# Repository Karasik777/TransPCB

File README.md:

# TransPCB

Agent-driven KiCad PCB design. You describe the board; Claude does schematic
capture, placement, autorouting and verification — under constraints you declare
once in a file.

Built by working a real board end to end, and hardened against every way that
went wrong. The [gotchas](docs/gotchas.md) are the actual value here: eight
documented failures that no upstream tool warns you about, three of which were
live on a board while KiCad DRC reported **zero errors**.

## What you get

- **7 Claude skills** — from-scratch design, routing, verification, optimisation,
  fab output, and the constraint system that ties them together
- **A constraint spec** — fab limits, net classes, differential pairs, via
  budgets, impedance targets, RF keepouts — declared once, pushed down to the
  autorouter, KiCad's rules, and the verifier
- **A verification suite** that catches what DRC misses: board-vs-schematic net
  drift, copper in RF keepouts, pair skew and via asymmetry, drill/annular DFM,
  missing ground planes, design-rule tampering — and **thermal**, which found
  the example board's regulator at 120 °C junction against a 125 °C limit
- **Thresholds derived from physics, not constants.** Declare `interface:
  usb2.0-fs` and the skew budget follows from the edge rate (20 mm), not from a
  number somebody typed
- **A crash guard** for a KiCad 10.0.5 segfault that kills the app mid-session
- **A placement critic** that reads your netlist and scores decoupling distance,
  decap ordering, connector edge access, crystal proximity and keepouts — with
  thresholds that tighten by frequency band
- **A placement optimiser** — simulated annealing against a tunable cost
  function. On the example board it cut copper 772→661 mm, vias 92→42, and
  moved the ESP32's decoupling cap from 22 mm to 4 mm from the pin it serves
- **Current-aware track widths** (IPC-2221) and a stackup gate, so an impedance
  target either uses your real stack or refuses to run
- **A fab package** gated on clean DRC — gerbers, drill, BOM, JLCPCB CPL
- **A worked example** — ESP32-C3 dev board, with its routing animation

## Install

```bash
git clone https://github.com/Karasik777/TransPCB && cd TransPCB
./setup/install.sh --project /path/to/your/board
```

Installs pinned versions of [`kicad-mcp-pro`](https://github.com/oaslananka/kicad-mcp-pro),
[`KiCadRoutingTools`](https://github.com/drandyhaas/KiCadRoutingTools), the
Freerouting container and the Python deps, then links the skills into
`~/.claude/skills/`. Nothing is vendored — upstream keeps its own updates.

Needs KiCad 9 or 10, `uv`, and optionally Docker. See [docs/mcp-setup.md](docs/mcp-setup.md).

## Use

```bash
cp constraints/example.yaml myboard/constraints.yaml    # edit it
```

Then just ask:

> Build me an ESP32-C3 dev board: USB-C power and native USB data, an efficient
> LDO, ESD protection, buttons, GPIO headers, test points. JLCPCB standard,
> 2 layers, as small as you can.

or, on a board that already exists:

> Route this board. Keep vias under 60, USB as a matched pair, ground plane on
> both layers, nothing under the antenna.

Anything after the verb belongs in `constraints.yaml` — say it once there and it
reaches the router, KiCad's rules and the verifier together.

## The loop

```
preflight  ->  commit  ->  apply constraints  ->  act  ->  verify  ->  commit
```

`git commit` before every routing run is not optional. Both autorouters and an
open pcbnew window have each silently destroyed a complete routing pass.

## Routers

| | Freerouting 2.1.0 | Rust A* |
|---|---|---|
| Routing violations | 1 unconnected, 2 dangling stubs | **0** |
| Copper | 958.3 mm | **691.7 mm** |
| Vias | **17** | 41 |
| Runtime | **58 s** (`-mp 20`, measured) | **0.18 s** — ~320x faster |
| Workflow | 2 manual GUI steps | none — reads `.kicad_pcb` |

Rust A* is the default. It also rewrites your design rules and discards copper
zones, so the workflow repairs both after every run — see
[pcb-route](skills/pcb-route/SKILL.md).

## Layout

```
skills/       Claude skills — the automation surface
scripts/
  kicad_sexp.py        s-expression reader/writer everything else builds on
  apply_constraints.py spec -> KiCad rules + router flags + IPC-2221 widths
  verify.py            net sync, keepouts, pair skew, DFM, planes, rule drift
  place_rules.py       placement critic, band-aware EE guidelines
  place_optimise.py    simulated-annealing placement refinement
  probe_footprint.py   pad axis, origin, courtyard, mating face — before placing
  fill_zones.py        headless zone fill (kicad-cli has none)
  fab_package.py       gerbers/drill/BOM/CPL, gated on clean DRC
  preflight.sh         crash guard + stale-buffer guard
constraints/  the spec schema, documented inline
docs/         MCP setup, gotchas, workflow
setup/        pinned installer, versions.lock
examples/     ESP32-C3 dev board + routing animation
```

## Credits

- [kicad-mcp-pro](https://github.com/oaslananka/kicad-mcp-pro) — Osman Aslan (MIT)
- [KiCadRoutingTools](https://github.com/drandyhaas/KiCadRoutingTools) — drandyhaas (MIT)
- [Freerouting](https://github.com/freerouting/freerouting) (GPL)
- [KiCad](https://kicad.org)

MIT. See [LICENSE](LICENSE).

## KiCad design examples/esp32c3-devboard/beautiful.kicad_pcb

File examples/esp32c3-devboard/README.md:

# ESP32-C3 dev board

The board TransPCB was built while making. 2 layers, 30 x 60 mm, JLCPCB standard.

## What's on it

- **U1** ESP32-C3-WROOM-02, antenna at the top board edge with a copper keepout
- **J3** USB-C, right-angle through-hole (GCT USB4085), 5.1k CC pulldowns
- **U3** USBLC6-2SC6 ESD clamp on D+/D- and VBUS
- **U2** AP2112K-3.3 LDO; CP1 100uF radial bulk, C4/C5 in, C6/C7 out
- Native USB Serial/JTAG on IO18/IO19 - **no UART bridge chip**
- RESET and BOOT buttons, power LED plus two user LEDs, six test points
- **J1/J2** 1x10 headers, pinout matched to the module's pin geography

## Header pinout

Deliberately arranged so each header carries the module pins physically nearest
it. Getting this wrong forces nets across the whole board and makes a 2-layer
route impossible without cutting the ground plane.

| J1 (left) | J2 (right) |
|---|---|
| 1 +3V3 · 2 GND | 1 +3V3 · 2 GND |
| 3 IO4 · 4 IO5 · 5 IO6 · 6 IO7 | 3 IO0 · 4 IO1 · 5 IO2 · 6 IO3 |
| 7 IO8 · 8 IO9 | 7 IO21/TX · 8 IO20/RX · 9 IO10 |
| 9 GND · 10 +3V3 | 10 EN |

## Reproducing

```bash
cp -r examples/esp32c3-devboard /tmp/demo && cd /tmp/demo
../../scripts/preflight.sh beautiful.kicad_pcb
python ../../scripts/verify.py beautiful.kicad_pcb --spec constraints.yaml --sch beautiful.kicad_sch
```

## Routing animation

`media/routing.gif` - 46 frames replaying the router's own event log
(`KICAD_ROUTE_TRACE=1`), showing traces laid, ripped and restored. Open it in a
browser; some image viewers show only the first frame.

## State

**0 DRC errors, 0 unconnected pads.** 5 of 6 TransPCB checks pass.

Placement was refined by `place_optimise.py` (simulated annealing) and fully
re-routed. Against the hand-placed original:

| | hand-placed | optimised |
|---|---|---|
| copper | 772.4 mm | **661.0 mm** |
| vias | 92 | **42** |
| ESP32 3V3 pin to nearest 100 nF | 22.00 mm | **4.09 mm** |
| DRC errors | 0 | **0** |

That last row is the one that matters: decoupling 22 mm from the pin it serves
is ornamental. It also drove four fixes in the optimiser - see the
`pcb-place` skill.

Routed with the two-stage flow - `route_diff.py` for the USB pair first, then
`route.py` for the rest. Pair skew: connector side 7.39 -> 3.26 mm, MCU side
13.42 -> 5.16 mm against a single-ended first attempt.

A board-level `ANTENNA_KEEPOUT` zone (tracks, vias and pour not allowed) keeps
the RF region clear - the router respects it, rather than the verifier catching
intrusions afterwards. Its boundary is y=61.5 rather than the footprint's 61.9,
because U1's own pads sit at y=62.0 and a 0.4 mm track reaching them spans
61.8..62.2.

### The one accepted failure

`diffpair:USB` - copper skew **2.89 mm** against a 2.5 mm threshold
(`USB_DP` 85.19 mm / 2 vias, `USB_DM` 82.29 mm / 4 vias).

This is the term that regressed when placement was optimised for decoupling:
skew was 1.52 mm before. A deliberate trade, and the right one here - at 12 Mbps
full-speed a bit period is 83 ns, and 2.9 mm of FR4 is roughly 19 ps, under
0.03% of a bit. USB 2.0 full speed also has no impedance-matching requirement;
that begins at high speed, 480 Mbps.

It would matter on a faster interface or in EMC testing. Fixing it properly
means placement work around TP3/TP4 and the ESD part, not re-routing.

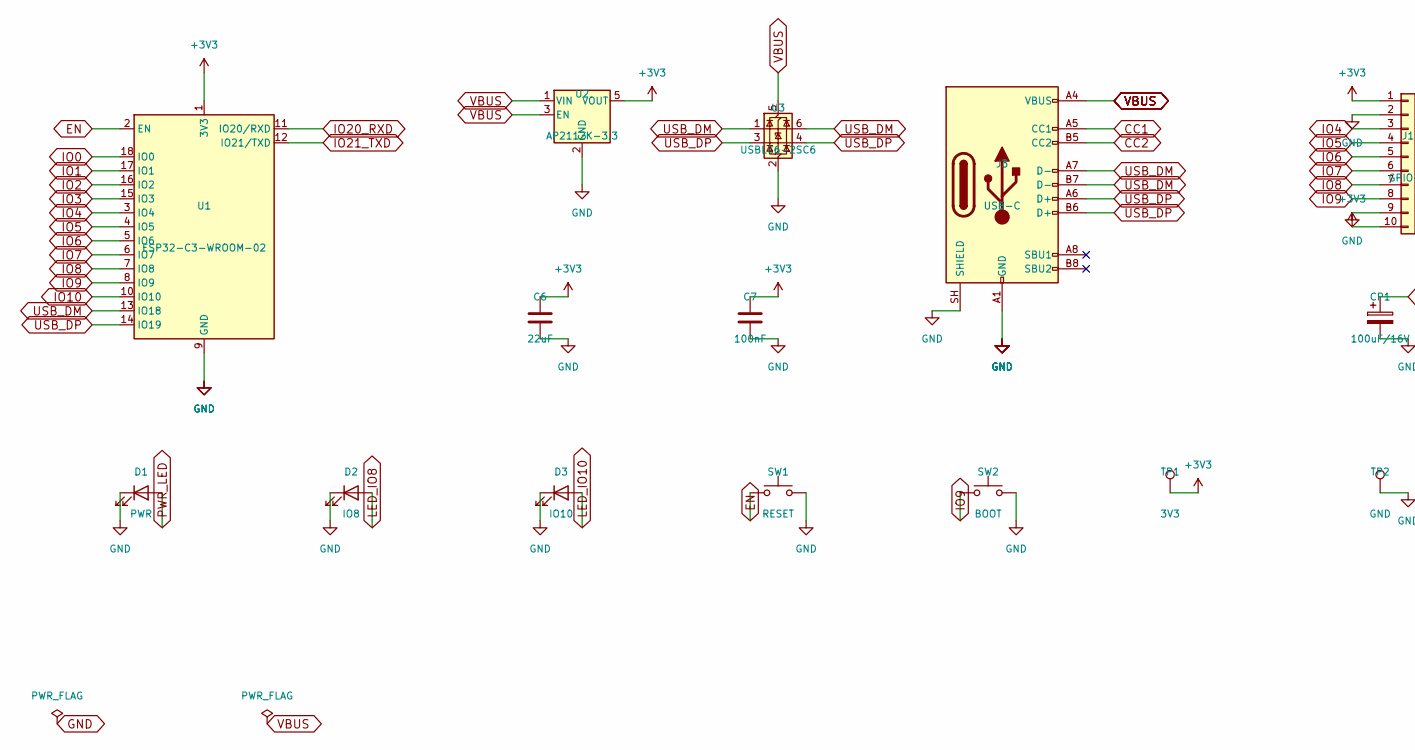
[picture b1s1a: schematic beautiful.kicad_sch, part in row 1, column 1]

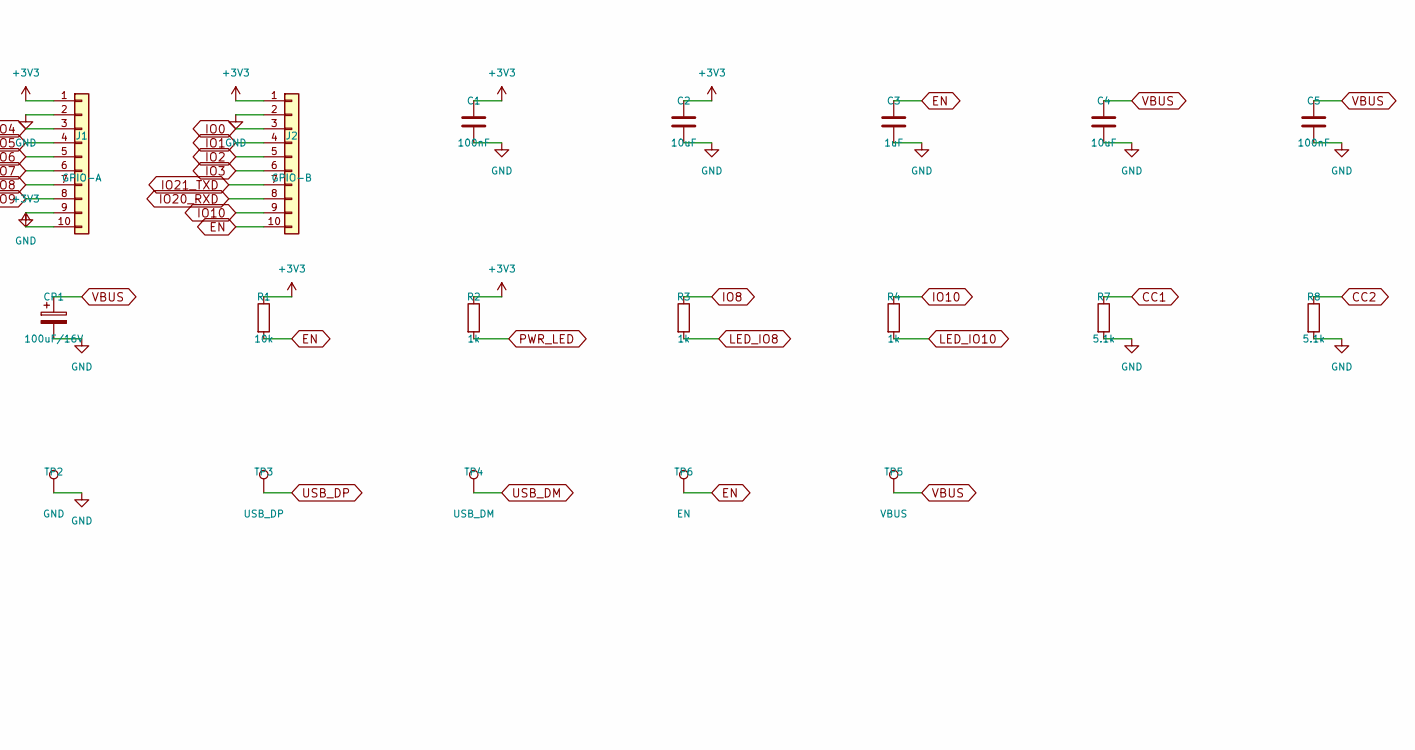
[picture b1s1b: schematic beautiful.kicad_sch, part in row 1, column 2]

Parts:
C1, C5, C7: 100nF; C_0603_1608Metric
C2, C4: 10uF; C_0805_2012Metric
C3: 1uF; C_0603_1608Metric
C6: 22uF; C_0805_2012Metric
CP1: 100uF/16V; CP_Radial_D6.3mm_P2.50mm
D1: PWR; LED_0603_1608Metric
D2: IO8; LED_0603_1608Metric
D3: IO10; LED_0603_1608Metric
J1: GPIO-A; PinHeader_1x10_P2.54mm_Vertical
J2: GPIO-B; PinHeader_1x10_P2.54mm_Vertical
J3: USB-C; USB_C_Receptacle_GCT_USB4085
R1: 10k; R_0603_1608Metric
R2, R3, R4: 1k; R_0603_1608Metric
R7, R8: 5.1k; R_0603_1608Metric
SW1: RESET; Panasonic_EVQPUJ_EVQPUA
SW2: BOOT; Panasonic_EVQPUJ_EVQPUA
TP1: 3V3; TestPoint_Pad_D1.5mm
TP2: GND; TestPoint_Pad_D1.5mm
TP3: USB_DP; TestPoint_Pad_D1.5mm
TP4: USB_DM; TestPoint_Pad_D1.5mm
TP5: VBUS; TestPoint_Pad_D1.5mm
TP6: EN; TestPoint_Pad_D1.5mm
U1: ESP32-C3-WROOM-02
U2: AP2112K-3.3; SOT-23-5
U3: USBLC6-2SC6; SOT-23-6

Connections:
+3V3: C1.1, C2.1, C6.1, C7.1, J1.1, J1.10, J2.1, R1.1, R2.1, TP1.1, U1.1 (3V3), U2.5 (VOUT)
CC1: J3.A5 (CC1), R7.1
CC2: J3.B5 (CC2), R8.1
EN: C3.1, J2.10, R1.2, SW1.1, TP6.1, U1.2 (EN)
GND: C1.2, C2.2, C3.2, C4.2, C5.2, C6.2, C7.2, CP1.2, D1.1 (K), D2.1 (K), D3.1 (K), J1.2, J1.9, J2.2, J3.A1 (GND), J3.A12 (GND), J3.B1 (GND), J3.B12 (GND), J3.SH (SHIELD), R7.2, R8.2, SW1.2, SW2.2, TP2.1, U1.9 (GND), U1.19 (GND), U2.2 (GND), U3.2 (GND)
IO0: J2.3, U1.18 (IO0)
IO1: J2.4, U1.17 (IO1)
IO2: J2.5, U1.16 (IO2)
IO3: J2.6, U1.15 (IO3)
IO4: J1.3, U1.3 (IO4)
IO5: J1.4, U1.4 (IO5)
IO6: J1.5, U1.5 (IO6)
IO7: J1.6, U1.6 (IO7)
IO8: J1.7, R3.1, U1.7 (IO8)
IO9: J1.8, SW2.1, U1.8 (IO9)
IO10: J2.9, R4.1, U1.10 (IO10)
IO20_RXD: J2.8, U1.11 (IO20/RXD)
IO21_TXD: J2.7, U1.12 (IO21/TXD)
LED_IO8: D2.2 (A), R3.2
LED_IO10: D3.2 (A), R4.2
PWR_LED: D1.2 (A), R2.2
USB_DM: J3.A7 (D-), J3.B7 (D-), TP4.1, U1.13 (IO18), U3.1 (I/O1), U3.6 (I/O1)
USB_DP: J3.A6 (D+), J3.B6 (D+), TP3.1, U1.14 (IO19), U3.3 (I/O2), U3.4 (I/O2)
VBUS: C4.1, C5.1, CP1.1, J3.A4 (VBUS), J3.A9 (VBUS), J3.B4 (VBUS), J3.B9 (VBUS), TP5.1, U2.1 (VIN), U2.3 (EN), U3.5 (VBUS)

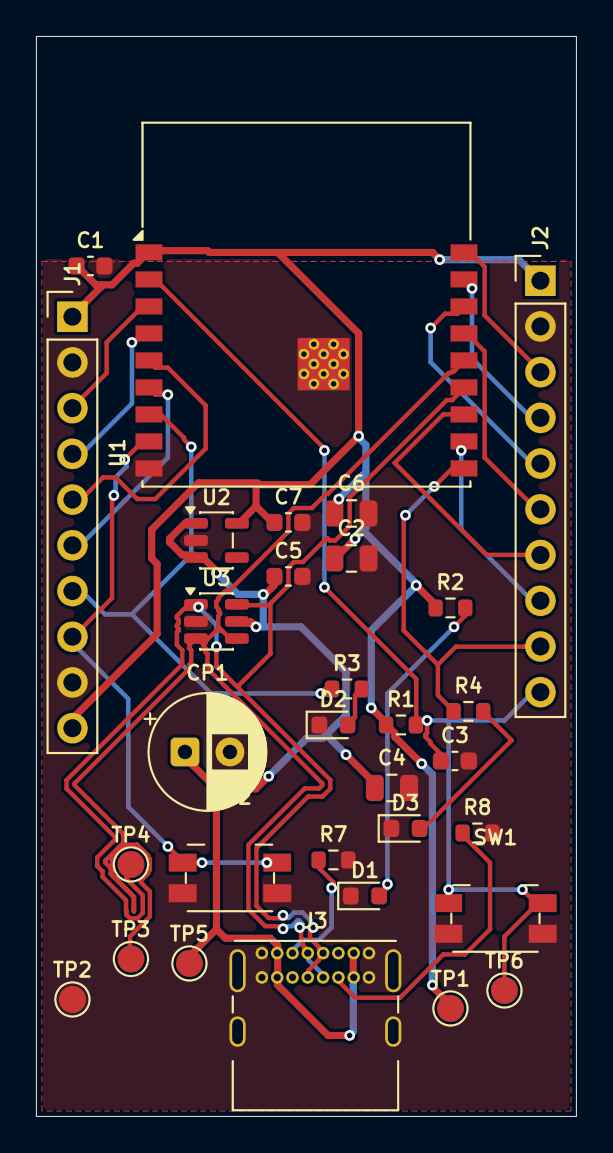
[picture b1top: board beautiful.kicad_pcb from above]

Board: 2 copper layers, 30.0 x 60.0 mm, 31 parts (0 on the bottom side), 24 nets.
